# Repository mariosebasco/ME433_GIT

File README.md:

# Advanced Mechatronics Course at NU

## Projects

Visit <a href="https://mariosebasco.github.io/"><u> my portfolio </u></a> for more information on some of the projects and assigments.

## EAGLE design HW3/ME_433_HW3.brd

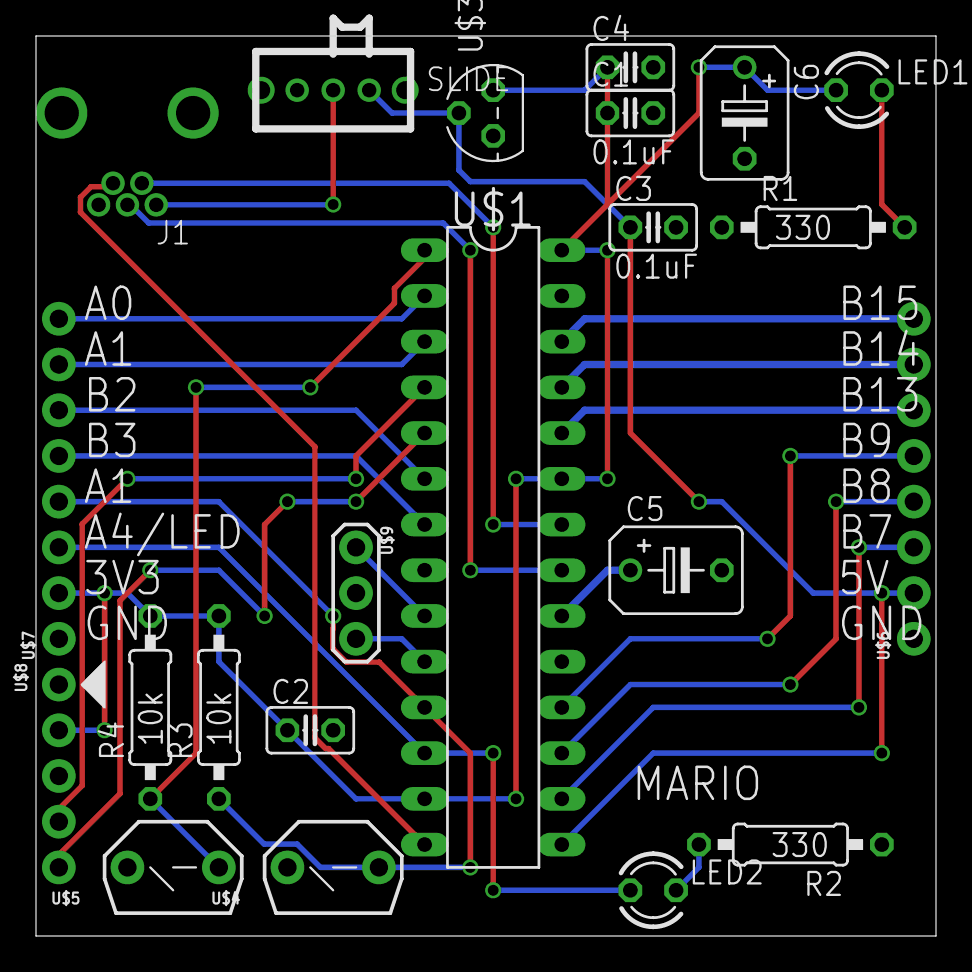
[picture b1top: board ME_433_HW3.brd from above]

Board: 2 copper layers, 50.0 x 50.0 mm, 22 parts (0 on the bottom side), 27 nets.

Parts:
C1, C2, C3, C4: 0.1uF; C025-025X050
C5, C6: 10uF; B45181B
J1: USB-MB-H
LED1: Red; LED3MM
LED2: Green; LED3MM
R1, R2: 330; 0207/10
R3, R4: 10k; 0207/10
U$1: PIC32MX250; DIL28-3
U$2: SLIDE
U$3: MCP1702; TO92
U$4: RESET; PB
U$5: USER; PB
U$6, U$7: CONN_08; 1X08
U$8: PICKIT3; 1X05
U$9: 8MHz; OSC

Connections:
+3V3: C1.1, C2.1, C4.1, C6.+, LED1.A, R3.2, R4.2, U$1.13, U$1.23, U$1.28, U$3.3, U$7.2, U$8.2
+5V: C3.1, U$1.15, U$2.3, U$3.2, U$6.2
A0: U$1.2, U$7.8
A1: U$1.3, U$7.7
A4/LED: LED2.A, U$1.12, U$7.3
B2: U$1.6, U$7.6
B3: U$1.7, U$7.5
B4/USER: R3.1, U$1.11, U$4.1, U$7.4
B7: U$1.16, U$6.3
B8: U$1.17, U$6.4
B9: U$1.18, U$6.5
B13: U$1.24, U$6.6
B14: U$1.25, U$6.7
B15: U$1.26, U$6.8
D+: J1.D+, U$1.21
D-: J1.D-, U$1.22
GND: C1.2, C2.2, C3.2, C4.2, C5.-, C6.-, J1.GND, R1.1, R2.1, U$1.8, U$1.19, U$1.27, U$3.1, U$4.2, U$5.2, U$6.1, U$7.1, U$8.3, U$9.2
MCLR: R4.1, U$1.1, U$5.1
unnamed: J1.VBUS, U$2.2
unnamed: U$1.9, U$9.1
unnamed: U$1.10, U$9.3
unnamed: LED1.K, R1.2
unnamed: LED2.K, R2.2
unnamed: C5.+, U$1.20
PGC: U$1.5, U$8.5
PGD: U$1.4, U$8.4
USBID: J1.ID, U$1.14

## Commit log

2017-03-29 Changed all the bist
2017-03-30 added some stuff
2017-03-30 added le pictures
2017-03-30 final changes
2017-04-04 added hw2
2017-04-07 Added hw3 .brd file and gerber files
2017-04-11 Added HW 4
2017-04-23 Added HW5
2017-04-23 added circuit diagram
2017-04-23 Added HW6, everything should be working fine
2017-04-24 Changes to main.c -- Fixed FPS output
2017-04-28 Started working on HW7, missing bars to the LCD
2017-04-29 Fixed unsigned char bug
2017-04-29 Finished HW7
2017-04-29 Completed HW 8
2017-05-01 Finished HW9
2017-05-06 Uploading HW 10 with matlab code and readme file
2017-05-13 Implemented code for HW11
2017-05-13 Added readme to hw11
2017-05-14 Did The Hello World App, with the slider and textView
2017-05-14 new foldrers, Also added HW13 - Camera App for Android
2017-05-14 Messing around with colors
2017-05-21 Finished HW14
2017-05-21 Added images to HW15
2017-05-21 added photos of wheel
2017-05-27 Added images of 3 sided box
2017-06-08 Adding final project code
2017-06-08 Added android code
2019-06-09 added link to projects
